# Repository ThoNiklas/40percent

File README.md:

# 40 percent
Complete design of a 40 % keyboard with 45 keys.

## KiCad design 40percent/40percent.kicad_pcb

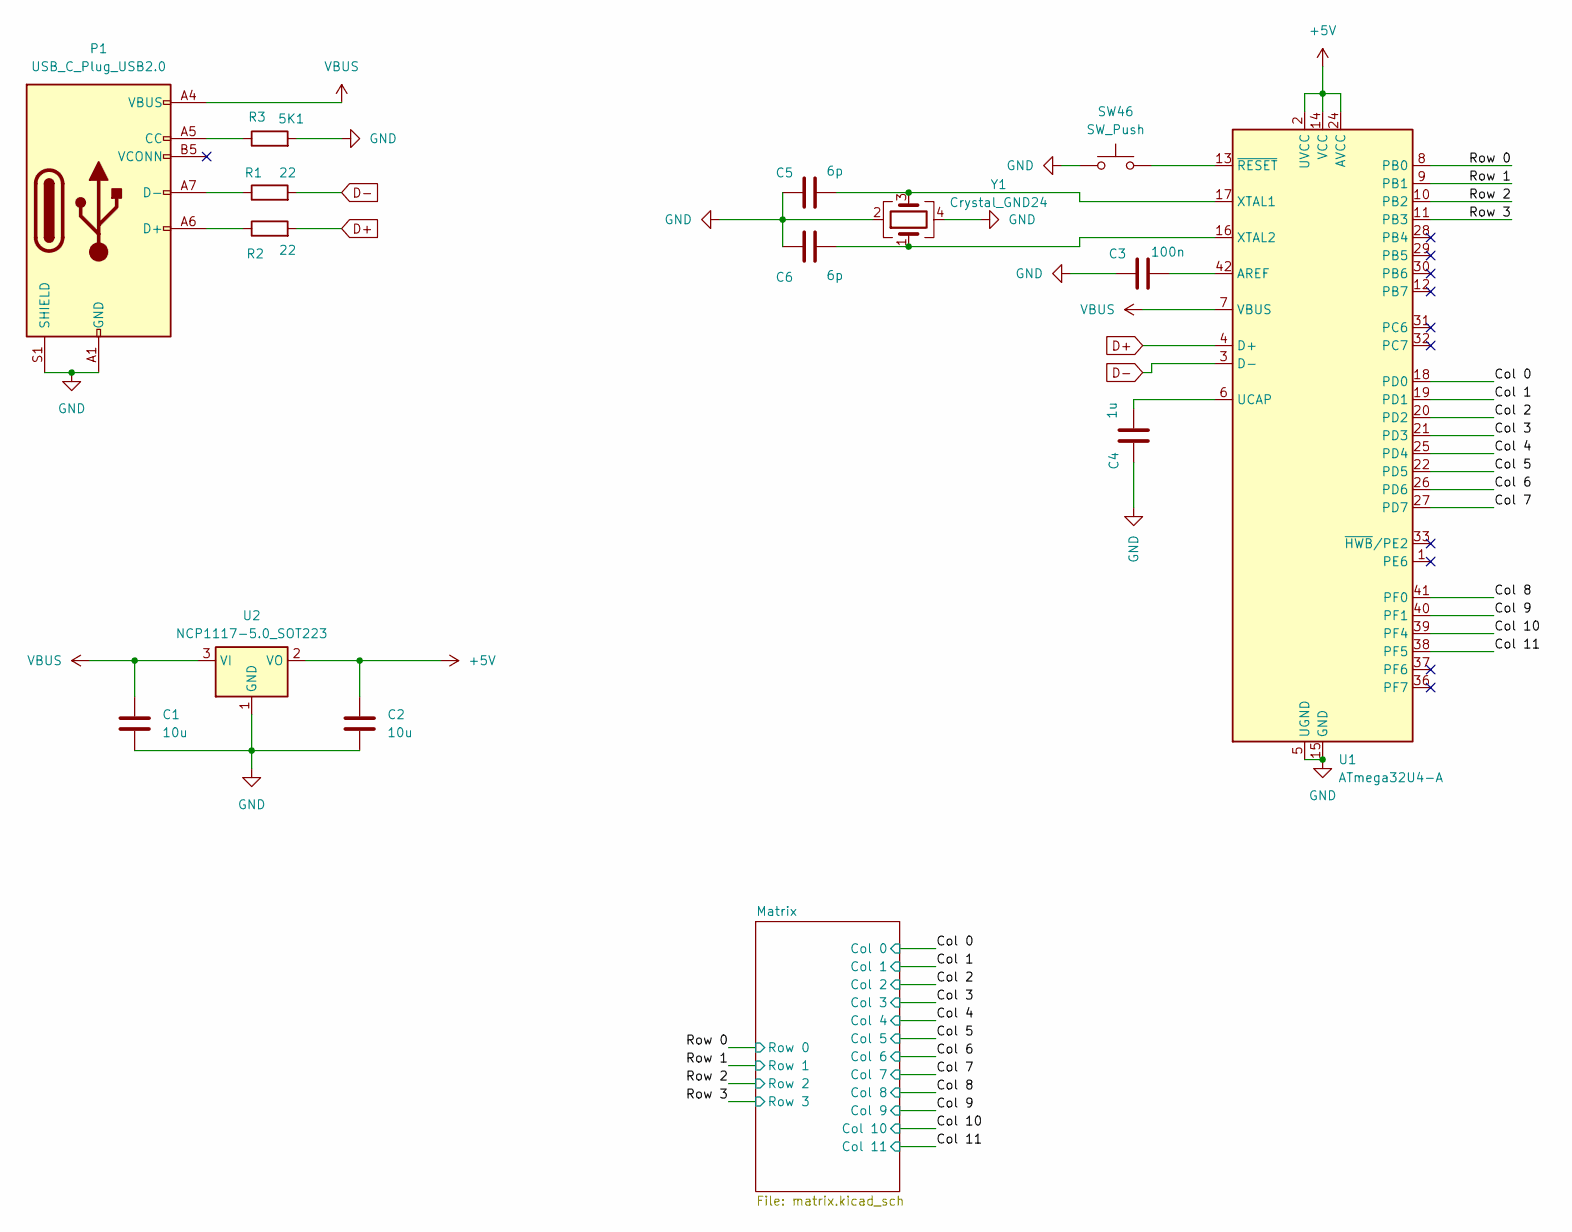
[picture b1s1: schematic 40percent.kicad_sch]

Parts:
C1, C2: 10u; C_0805_2012Metric_Pad1.18x1.45mm_HandSolder
C3: 100n; C_0805_2012Metric_Pad1.18x1.45mm_HandSolder
C4: 1u; C_0805_2012Metric_Pad1.18x1.45mm_HandSolder
C5, C6: 6p; C_0805_2012Metric_Pad1.18x1.45mm_HandSolder
P1: USB_C_Plug_USB2.0; USB_C_Receptacle_HRO_TYPE-C-31-M-12
R1, R2: 22; R_0402_1005Metric_Pad0.72x0.64mm_HandSolder
R3: 5K1; R_0402_1005Metric_Pad0.72x0.64mm_HandSolder
SW46: SW_Push; SW_SPST_TL3342
U1: ATmega32U4-A; TQFP-44_10x10mm_P0.8mm
U2: NCP1117-5.0_SOT223; SOT-223-3_TabPin2
Y1: Crystal_GND24; Crystal_SMD_3225-4Pin_3.2x2.5mm_HandSoldering

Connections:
+5V: C2.1, U1.2 (UVCC), U1.14 (VCC), U1.24 (AVCC), U1.34 (VCC), U1.44 (AVCC), U2.2 (VO)
/Col 0: U1.18 (PD0); also elsewhere on the board
/Col 1: U1.19 (PD1); also elsewhere on the board
/Col 2: U1.20 (PD2); also elsewhere on the board
/Col 3: U1.21 (PD3); also elsewhere on the board
/Col 4: U1.25 (PD4); also elsewhere on the board
/Col 5: U1.22 (PD5); also elsewhere on the board
/Col 6: U1.26 (PD6); also elsewhere on the board
/Col 7: U1.27 (PD7); also elsewhere on the board
/Col 8: U1.41 (PF0); also elsewhere on the board
/Col 9: U1.40 (PF1); also elsewhere on the board
/Col 10: U1.39 (PF4); also elsewhere on the board
/Col 11: U1.38 (PF5); also elsewhere on the board
/Row 0: U1.8 (PB0); also elsewhere on the board
/Row 1: U1.9 (PB1); also elsewhere on the board
/Row 2: U1.10 (PB2); also elsewhere on the board
/Row 3: U1.11 (PB3); also elsewhere on the board
D+: R2.2, U1.4 (D+)
D-: R1.2, U1.3 (D-)
GND: C1.2, C2.2, C3.1, C4.1, C5.1, C6.1, P1.A1 (GND), P1.A12 (GND), P1.B1 (GND), P1.B12 (GND), P1.S1 (SHIELD), R3.2, SW46.1, U1.5 (UGND), U1.15 (GND), U1.23 (GND), U1.35 (GND), U1.43 (GND), U2.1 (GND), Y1.2, Y1.4
unnamed: P1.A5 (CC), R3.1
unnamed: P1.A6 (D+), R2.1
unnamed: P1.A7 (D-), R1.1
unnamed: C3.2, U1.42 (AREF)
unnamed: C4.2, U1.6 (UCAP)
unnamed: C5.2, U1.17 (XTAL1), Y1.3
unnamed: C6.2, U1.16 (XTAL2), Y1.1
unnamed: SW46.2, U1.13 (~RESET)
VBUS: C1.1, P1.A4 (VBUS), P1.A9 (VBUS), P1.B4 (VBUS), P1.B9 (VBUS), U1.7 (VBUS), U2.3 (VI)

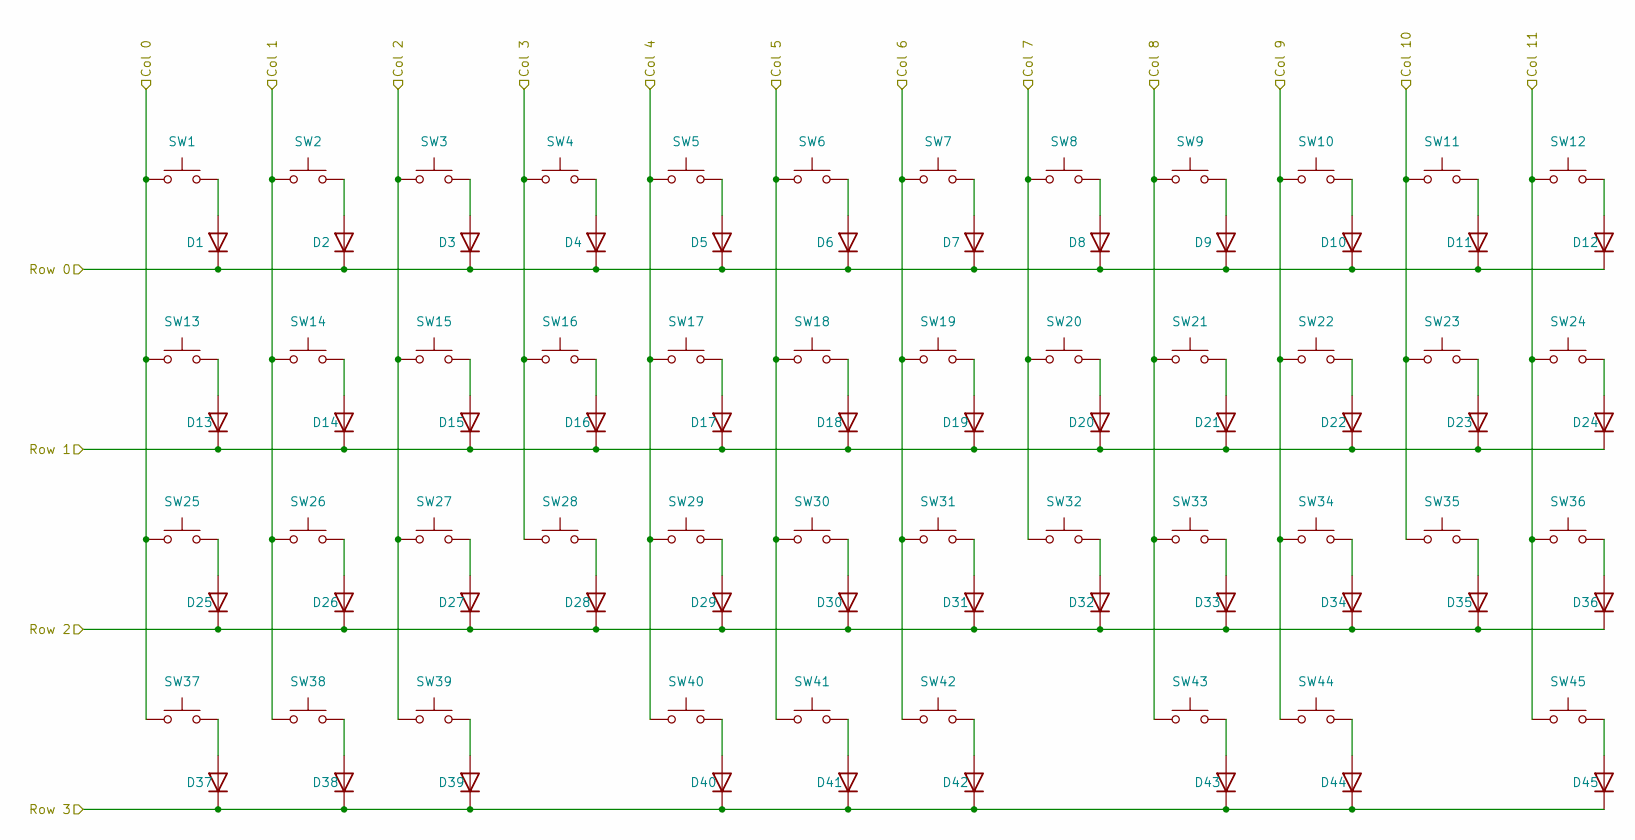
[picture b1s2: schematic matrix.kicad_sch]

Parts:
D1, D2, D3, D4, D5, D6, D7, D8, D9, D10, D11, D12, D13, D14, D15, D16, D17, D18, D19, D20, D21, D22, D23, D24, D25, D26, D27, D28, D29, D30, D31, D32, D33, D34, D35, D36, D37, D38, D39, D40, D41, D42, D43, D44, D45: D; D_0805_2012Metric_Pad1.15x1.40mm_HandSolder
SW1, SW2, SW3, SW4, SW5, SW6, SW7, SW8, SW9, SW10, SW11, SW14, SW15, SW16, SW17, SW18, SW19, SW20, SW21, SW22, SW23, SW26, SW27, SW28, SW29, SW30, SW31, SW32, SW33, SW34, SW35, SW36, SW41: SW_Push; SW_Hotswap_Kailh_MX_1.00u
SW12, SW25: SW_Push; SW_Hotswap_Kailh_MX_2.00u
SW13, SW24, SW37, SW38, SW39, SW40, SW42, SW43, SW44, SW45: SW_Push; SW_Hotswap_Kailh_MX_1.50u

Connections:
/Col 0: SW1.1, SW13.1, SW25.1, SW37.1; also elsewhere on the board
/Col 1: SW2.1, SW14.1, SW26.1, SW38.1; also elsewhere on the board
/Col 2: SW3.1, SW15.1, SW27.1, SW39.1; also elsewhere on the board
/Col 3: SW4.1, SW16.1, SW28.1; also elsewhere on the board
/Col 4: SW5.1, SW17.1, SW29.1, SW40.1; also elsewhere on the board
/Col 5: SW6.1, SW18.1, SW30.1, SW41.1; also elsewhere on the board
/Col 6: SW7.1, SW19.1, SW31.1, SW42.1; also elsewhere on the board
/Col 7: SW8.1, SW20.1, SW32.1; also elsewhere on the board
/Col 8: SW9.1, SW21.1, SW33.1, SW43.1; also elsewhere on the board
/Col 9: SW10.1, SW22.1, SW34.1, SW44.1; also elsewhere on the board
/Col 10: SW11.1, SW23.1, SW35.1; also elsewhere on the board
/Col 11: SW12.1, SW24.1, SW36.1, SW45.1; also elsewhere on the board
/Row 0: D1.1 (K), D2.1 (K), D3.1 (K), D4.1 (K), D5.1 (K), D6.1 (K), D7.1 (K), D8.1 (K), D9.1 (K), D10.1 (K), D11.1 (K), D12.1 (K); also elsewhere on the board
/Row 1: D13.1 (K), D14.1 (K), D15.1 (K), D16.1 (K), D17.1 (K), D18.1 (K), D19.1 (K), D20.1 (K), D21.1 (K), D22.1 (K), D23.1 (K), D24.1 (K); also elsewhere on the board
/Row 2: D25.1 (K), D26.1 (K), D27.1 (K), D28.1 (K), D29.1 (K), D30.1 (K), D31.1 (K), D32.1 (K), D33.1 (K), D34.1 (K), D35.1 (K), D36.1 (K); also elsewhere on the board
/Row 3: D37.1 (K), D38.1 (K), D39.1 (K), D40.1 (K), D41.1 (K), D42.1 (K), D43.1 (K), D44.1 (K), D45.1 (K); also elsewhere on the board
unnamed: D1.2 (A), SW1.2
unnamed: D2.2 (A), SW2.2
unnamed: D3.2 (A), SW3.2
unnamed: D4.2 (A), SW4.2
unnamed: D5.2 (A), SW5.2
unnamed: D6.2 (A), SW6.2
unnamed: D7.2 (A), SW7.2
unnamed: D8.2 (A), SW8.2
unnamed: D9.2 (A), SW9.2
unnamed: D10.2 (A), SW10.2
unnamed: D11.2 (A), SW11.2
unnamed: D12.2 (A), SW12.2
unnamed: D13.2 (A), SW13.2
unnamed: D14.2 (A), SW14.2
unnamed: D15.2 (A), SW15.2
unnamed: D16.2 (A), SW16.2
unnamed: D17.2 (A), SW17.2
unnamed: D18.2 (A), SW18.2
unnamed: D19.2 (A), SW19.2
unnamed: D20.2 (A), SW20.2
unnamed: D21.2 (A), SW21.2
unnamed: D22.2 (A), SW22.2
unnamed: D23.2 (A), SW23.2
unnamed: D24.2 (A), SW24.2
unnamed: D25.2 (A), SW25.2
unnamed: D26.2 (A), SW26.2
unnamed: D27.2 (A), SW27.2
unnamed: D28.2 (A), SW28.2
unnamed: D29.2 (A), SW29.2
unnamed: D30.2 (A), SW30.2
unnamed: D31.2 (A), SW31.2
unnamed: D32.2 (A), SW32.2
unnamed: D33.2 (A), SW33.2
unnamed: D34.2 (A), SW34.2
unnamed: D35.2 (A), SW35.2
unnamed: D36.2 (A), SW36.2
unnamed: D37.2 (A), SW37.2
unnamed: D38.2 (A), SW38.2
unnamed: D39.2 (A), SW39.2
unnamed: D40.2 (A), SW40.2
unnamed: D41.2 (A), SW41.2
unnamed: D42.2 (A), SW42.2
unnamed: D43.2 (A), SW43.2
unnamed: D44.2 (A), SW44.2
unnamed: D45.2 (A), SW45.2

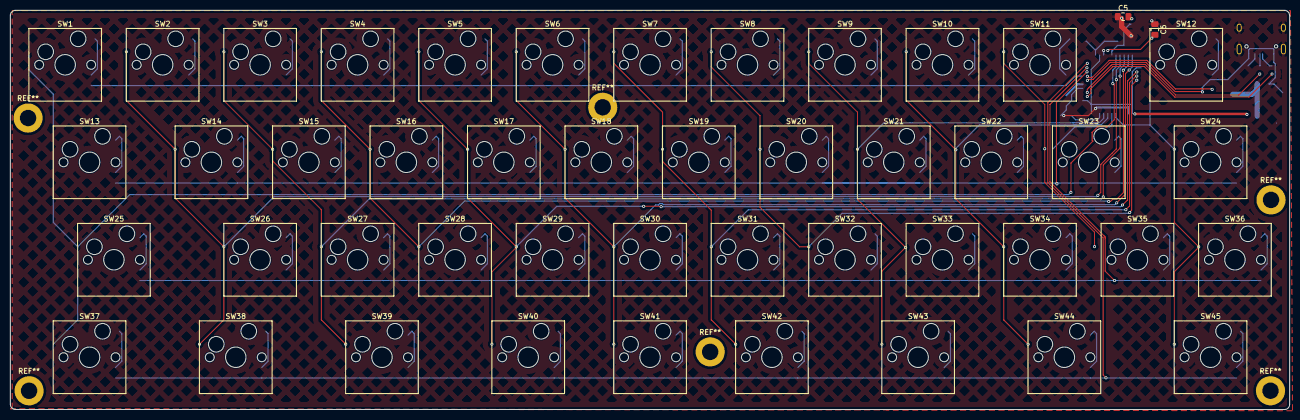
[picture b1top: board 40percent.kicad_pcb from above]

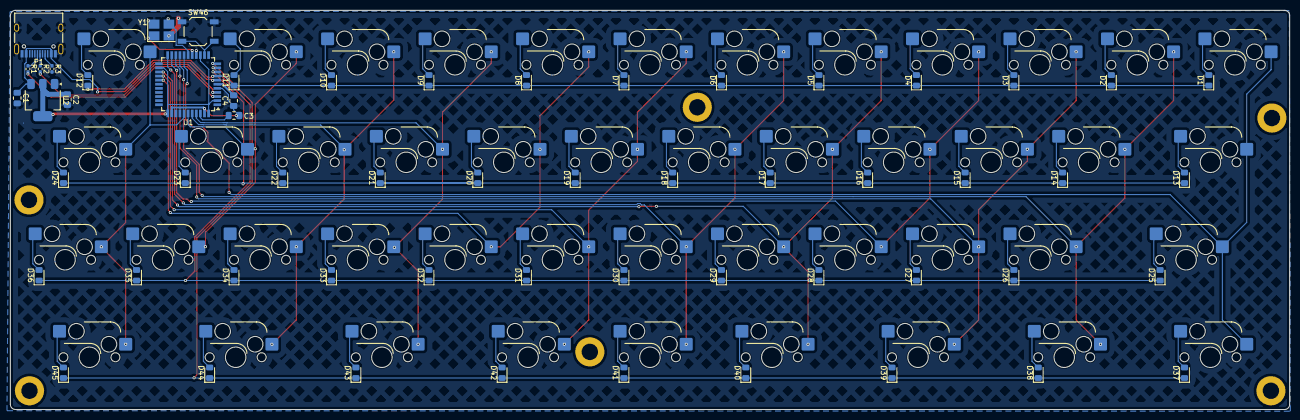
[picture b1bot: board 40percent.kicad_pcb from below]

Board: 2 copper layers, 250.0 x 78.0 mm, 104 parts (57 on the bottom side), 74 nets.

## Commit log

2025-06-15 Added pictures for readme
2025-06-15 Changed .gitignore, updated case
